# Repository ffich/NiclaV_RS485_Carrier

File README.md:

# 🔌 NiclaV_RS485_Carrier

A **compact and robust carrier board** for the **Arduino Nicla Vision**, designed with **KiCad 9**, ideal for industrial and harsh environments where **RS485 communication** and **daisy-chain topology** are required.

---

## 📦 Introduction

The **NiclaV_RS485_Carrier** is a breakout board tailored for the **Arduino Nicla Vision**, adding RS485 communication and 24 V power handling capabilities. It simplifies integration into industrial or distributed IoT systems.

---

## 🔧 Key Features

- ⚡ **24 V Power Input**  
  Input via screw terminal, regulated by a **Buck converter** to safely power the Nicla.

- 🔄 **Integrated RS485 Transceiver**  
  Robust half-duplex serial communication, suited for industrial use.

- 🔗 **Dual Power/RS485 Connectors (IN/OUT)**  
  Enables **daisy-chain** connections between multiple devices.

- 🔥 **120 Ω Termination Resistor**  
  On-board line termination, selectable via jumper.

- 💡 **Status LEDs**  
  - **Power LED** for board status  
  - **User LED** controllable from the Nicla (for debug or signaling)

- 🖨️ **Designed with KiCad 9**  
  Fully open-source hardware project.

---

## 🧠 Use Cases

- 👁️‍🗨️ Distributed machine vision systems using RS485  
- 🏭 Industrial sensor nodes  
- 📷 Smart camera networks in the field  
- 📡 IoT endpoints for harsh environments

---

## 🧪 Project Status

🟢 **Ready for testing**  
Waiting for first prototypes, electrical and functional validation and RS485 bus communication testing.

---

## 📸 Preview

---

## ⚙️ TODO

- [ ] Validate RS485 over long-distance bus  
- [ ] Field test with 24 V industrial power  
- [ ] Add termination switch option  
- [ ] Design a 3D-printed enclosure

---

## 📬 Contact

For questions, feedback, or collaboration proposals, feel free to open an issue or reach out directly!

---

💙 Open-source project made with **Arduino** passion.

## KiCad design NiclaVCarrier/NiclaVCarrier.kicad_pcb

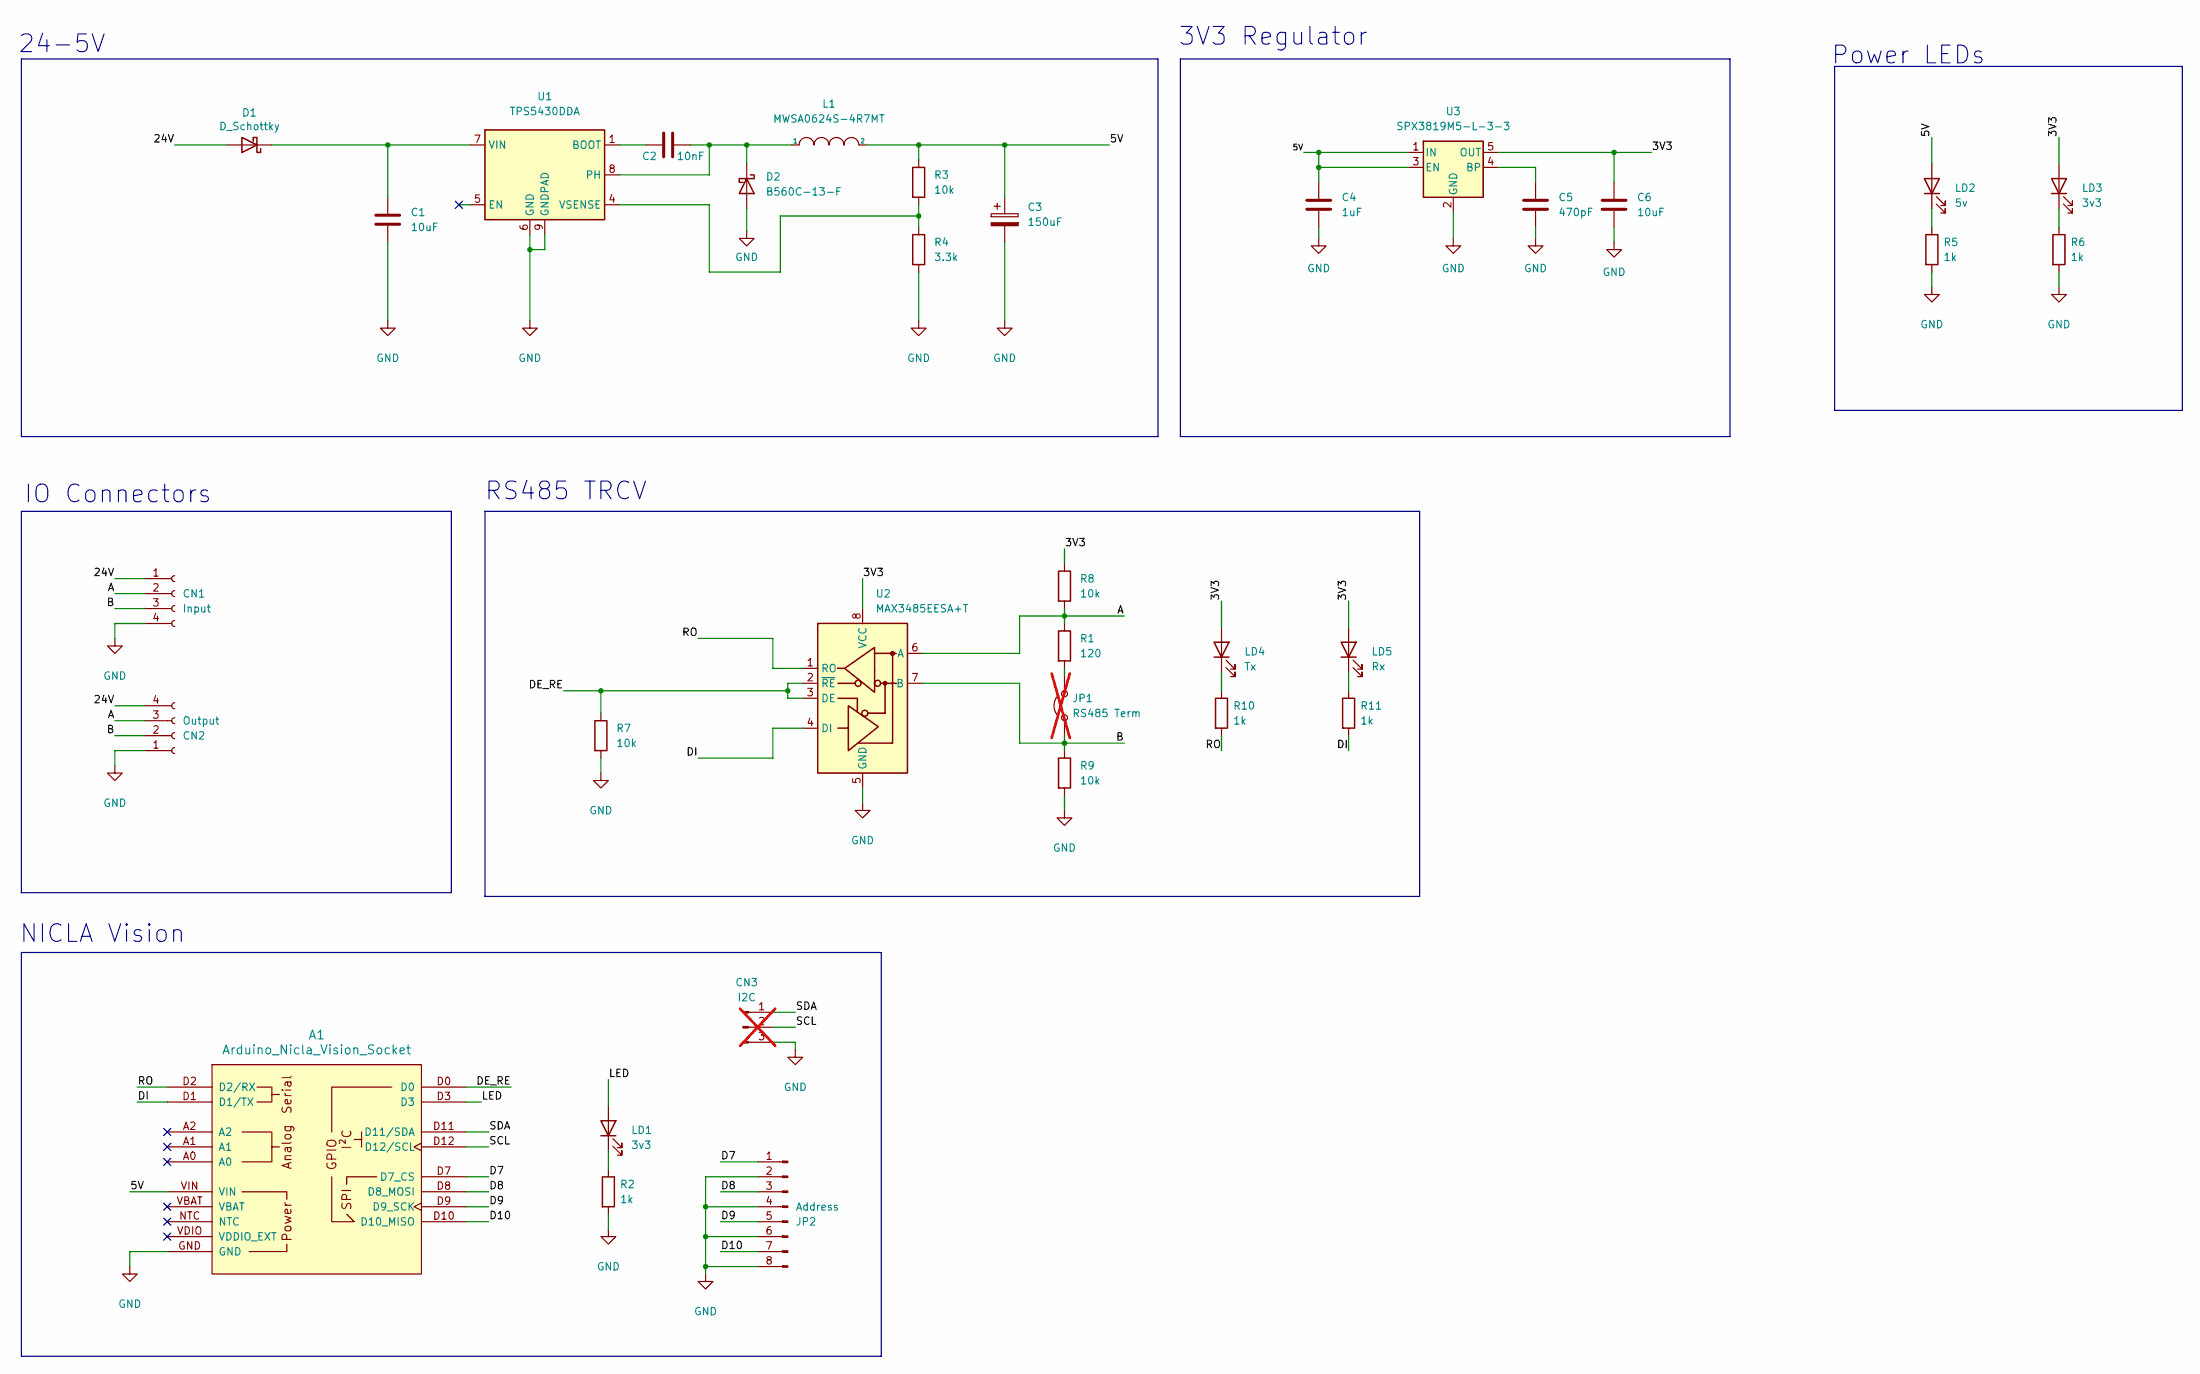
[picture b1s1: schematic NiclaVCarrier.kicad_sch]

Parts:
A1: Arduino_Nicla_Vision_Socket
C1: 10uF; C_1206_3216Metric; LCSC C13585
C2: 10nF; C_0402_1005Metric; LCSC C15195
C3: 150uF; CP_Elec_6.3x7.7; LCSC C7471880
C4: 1uF; C_0603_1608Metric; LCSC C15849
C5: 470pF; C_0402_1005Metric; LCSC C1537
C6: 10uF; C_0603_1608Metric; LCSC C96446
CN1: Input; PhoenixContact_MSTBA_2,5_4-G-5,08_1x04_P5.08mm_Horizontal; LCSC C192796
CN2: Output; PhoenixContact_MSTBA_2,5_4-G-5,08_1x04_P5.08mm_Horizontal; LCSC C192796
CN3: I2C; PinHeader_1x03_P2.54mm_Vertical; not fitted
D1: D_Schottky; D_SMA; LCSC C412514
D2: B560C-13-F; D_SMC; LCSC C85100
JP1: RS485 Term; PinHeader_1x02_P2.54mm_Vertical; not fitted
JP2: Address; PinHeader_2x04_P2.54mm_Vertical; LCSC C225289
L1: MWSA0624S-4R7MT; L_Bourns_SRP7028A_7.3x6.6mm; LCSC C408433
LD1, LD3: 3v3; LED_0603_1608Metric; LCSC C2286
LD2: 5v; LED_0603_1608Metric; LCSC C2286
LD4: Tx; LED_0603_1608Metric; LCSC C2286
LD5: Rx; LED_0603_1608Metric; LCSC C2286
R1: 120; R_0603_1608Metric; LCSC C177328
R2, R5, R6, R10, R11: 1k; R_0402_1005Metric; LCSC C140196
R3, R7, R8, R9: 10k; R_0805_2012Metric; LCSC C17414
R4: 3.3k; R_0805_2012Metric; LCSC C26010
U1: TPS5430DDA; TI_SO-PowerPAD-8_ThermalVias; LCSC C9864
U2: MAX3485EESA+T; SOIC-8_3.9x4.9mm_P1.27mm; LCSC C9943
U3: SPX3819M5-L-3-3; SOT-23-5; LCSC C9055

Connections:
/3V3: C6.1, LD3.2 (A), LD4.2 (A), LD5.2 (A), R8.1, U2.8 (VCC), U3.5 (OUT)
/5V: A1.VIN, C3.1, C4.1, L1.2, LD2.2 (A), R3.1, U3.1 (IN), U3.3 (EN)
/24V: CN1.1, CN2.4, D1.2 (A)
/A: CN1.2, CN2.3, R1.1, R8.2, U2.6 (A)
/B: CN1.3, CN2.2, JP1.1 (A), R9.1, U2.7 (B)
/D7: A1.D7 (D7_CS), JP2.1
/D8: A1.D8 (D8_MOSI), JP2.3
/D9: A1.D9 (D9_SCK), JP2.5
/D10: A1.D10 (D10_MISO), JP2.7
/DE_RE: A1.D0, R7.1, U2.2 (~RE), U2.3 (DE)
/DI: A1.D1 (D1/TX), R11.2, U2.4 (DI)
/LED: A1.D3, LD1.2 (A)
/RO: A1.D2 (D2/RX), R10.2, U2.1 (RO)
/SCL: A1.D12 (D12/SCL), CN3.2
/SDA: A1.D11 (D11/SDA), CN3.1
GND: A1.GND, C1.2, C3.2, C4.2, C5.2, C6.2, CN1.4, CN2.1, CN3.3, D2.2 (A), JP2.2, JP2.4, JP2.6, JP2.8, R2.2, R4.2, R5.2, R6.2, R7.2, R9.2, U1.6 (GND), U1.9 (GNDPAD), U2.5 (GND), U3.2 (GND)
unnamed: C1.1, D1.1 (K), U1.7 (VIN)
unnamed: C2.1, D2.1 (K), L1.1, U1.8 (PH)
unnamed: JP1.2 (B), R1.2
unnamed: LD1.1 (K), R2.1
unnamed: LD2.1 (K), R5.1
unnamed: LD3.1 (K), R6.1
unnamed: LD4.1 (K), R10.1
unnamed: LD5.1 (K), R11.1
unnamed: C2.2, U1.1 (BOOT)
unnamed: R3.2, R4.1, U1.4 (VSENSE)
unnamed: C5.1, U3.4 (BP)

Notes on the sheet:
RS485 TRCV
3V3 Regulator
NICLA Vision
Power LEDs
24-5V
IO Connectors

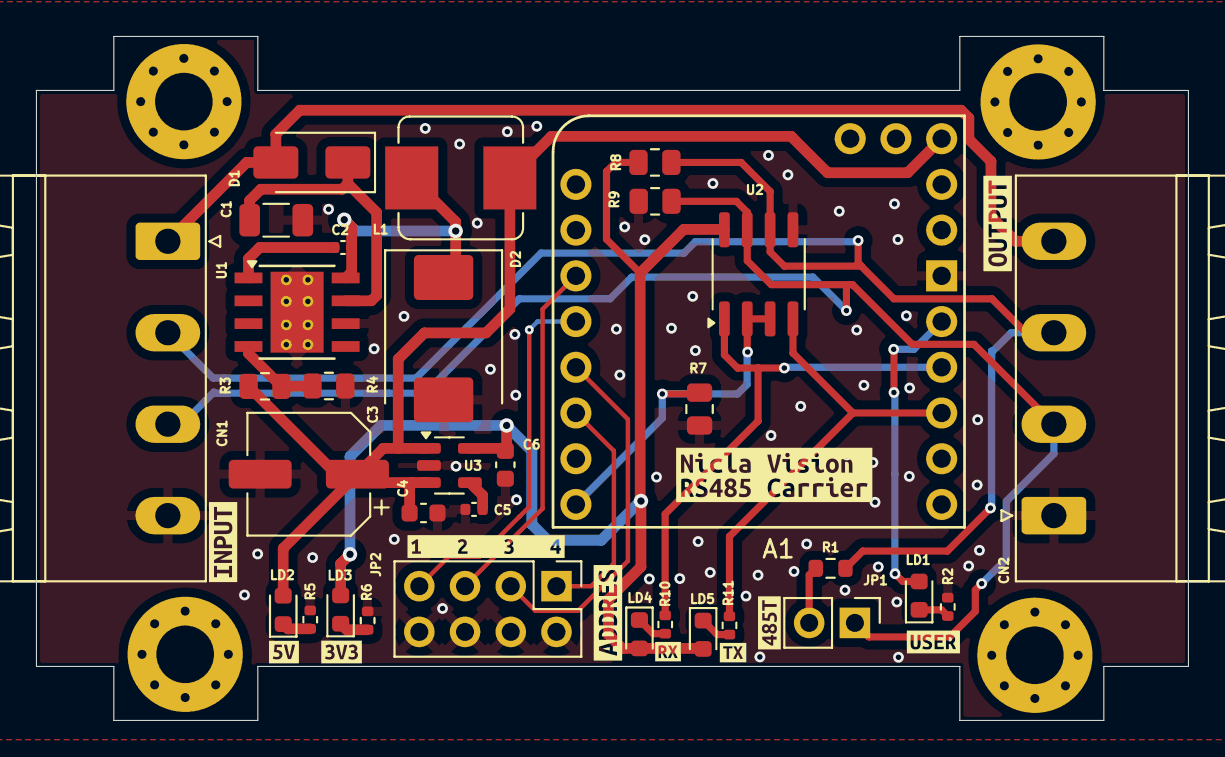
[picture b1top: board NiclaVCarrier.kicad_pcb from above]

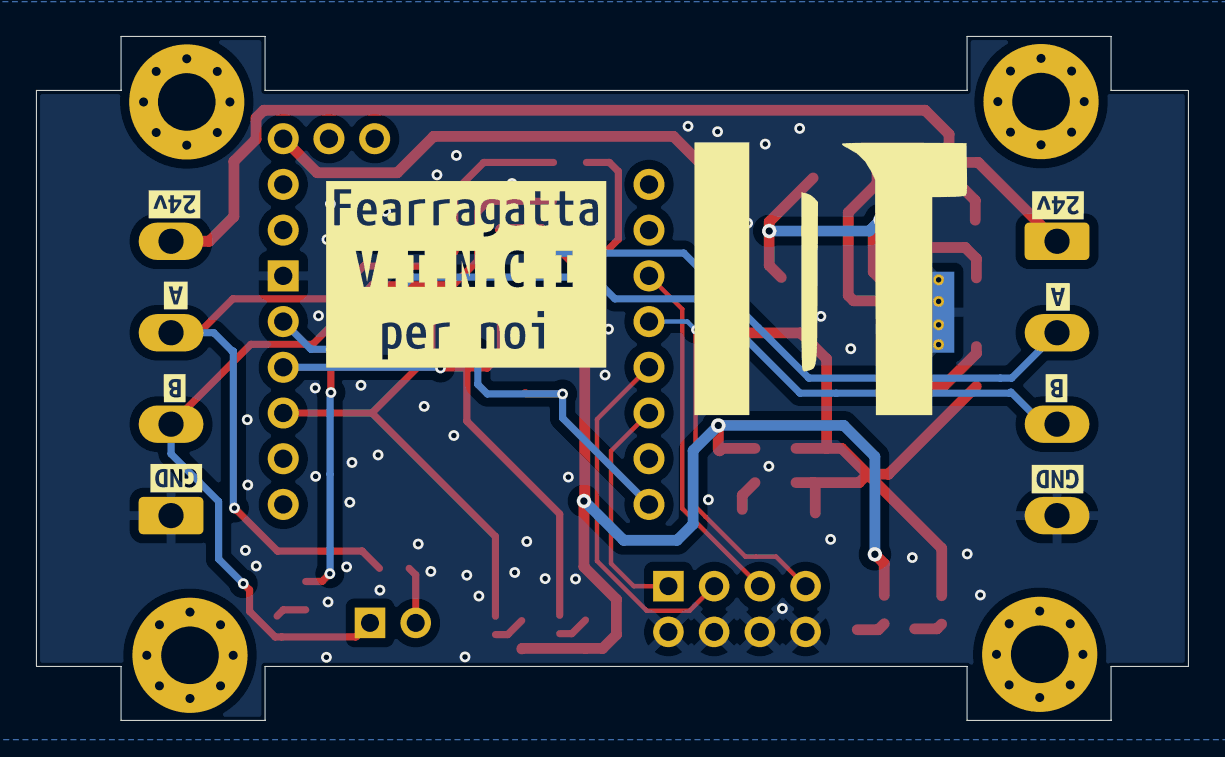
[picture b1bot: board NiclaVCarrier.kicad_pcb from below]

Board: 4 copper layers, 64.0 x 38.0 mm, 53 parts (9 on the bottom side), 25 nets.

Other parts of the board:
kibuzzard-687D11A9: G***; kibuzzard-687D11A9
kibuzzard-687D11CA: G***; kibuzzard-687D11CA
kibuzzard-687D13F1: G***; kibuzzard-687D13F1
kibuzzard-687D22F4: G***; kibuzzard-687D22F4
kibuzzard-687D118B: G***; kibuzzard-687D118B
kibuzzard-687D122C, kibuzzard-687D122C#2: G***; kibuzzard-687D122C
kibuzzard-687D124A, kibuzzard-687D124A#2: G***; kibuzzard-687D124A
kibuzzard-687D125B, kibuzzard-687D125B#2: G***; kibuzzard-687D125B
kibuzzard-687D131B: G***; kibuzzard-687D131B
kibuzzard-687D1205: G***; kibuzzard-687D1205
kibuzzard-687D1264, kibuzzard-687D1264#2: G***; kibuzzard-687D1264
kibuzzard-687D1379: G***; kibuzzard-687D1379
kibuzzard-687D1424: G***; kibuzzard-687D1424
kibuzzard-687E9AA8: G***; kibuzzard-687E9AA8
kibuzzard-687E9ABC: G***; kibuzzard-687E9ABC
kibuzzard-687E9791: G***; kibuzzard-687E9791

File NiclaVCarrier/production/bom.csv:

Designator,Footprint,Quantity,Value,LCSC Part #
A1,Arduino_Nicla_Vision_Socket,1,Arduino_Nicla_Vision_Socket,
C1,1206,1,10uF,C13585
C2,0402,1,10nF,C15195
C3,CP_Elec_6.3x7.7,1,150uF,C7471880
C4,0603,1,1uF,C15849
C5,0402,1,470pF,C1537
C6,0603,1,10uF,C96446
CN1,"PhoenixContact_MSTBA_2,5_4-G-5,08_1x04_P5.08mm_Horizontal",1,Input,C192796
CN2,"PhoenixContact_MSTBA_2,5_4-G-5,08_1x04_P5.08mm_Horizontal",1,Output,C192796
D1,D_SMA,1,D_Schottky,C412514
D2,D_SMC,1,B560C-13-F,C85100
JP2,PinHeader_2x04_P2.54mm_Vertical,1,Address,C225289
L1,L_Bourns_SRP7028A_7.3x6.6mm,1,MWSA0624S-4R7MT,C408433
"LD1, LD3",0603,2,3v3,C2286
LD2,0603,1,5v,C2286
LD4,0603,1,Tx,C2286
LD5,0603,1,Rx,C2286
R1,0603,1,120,C177328
"R10, R11, R2, R5, R6",0402,5,1k,C140196
"R3, R7, R8, R9",0805,4,10k,C17414
R4,0805,1,3.3k,C26010
U1,TI_SO-PowerPAD-8_ThermalVias,1,TPS5430DDA,C9864
U2,SOIC-8_3.9x4.9mm_P1.27mm,1,MAX3485EESA+T,C9943
U3,SOT-23-5,1,SPX3819M5-L-3-3,C9055

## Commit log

2025-07-20 Update README.md
    Added description
2025-07-20 Update README.md
    minor
2025-07-21 Updated design
2025-08-24 Added basic driver support
2025-08-24 added example description
2025-08-24 Added Modbus RTU Slave implementation
